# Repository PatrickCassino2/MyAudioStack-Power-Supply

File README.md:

# MyAudioStack-Power-Supply
A +/- 17V Offline Power Supply Compatible with MyAudioStack

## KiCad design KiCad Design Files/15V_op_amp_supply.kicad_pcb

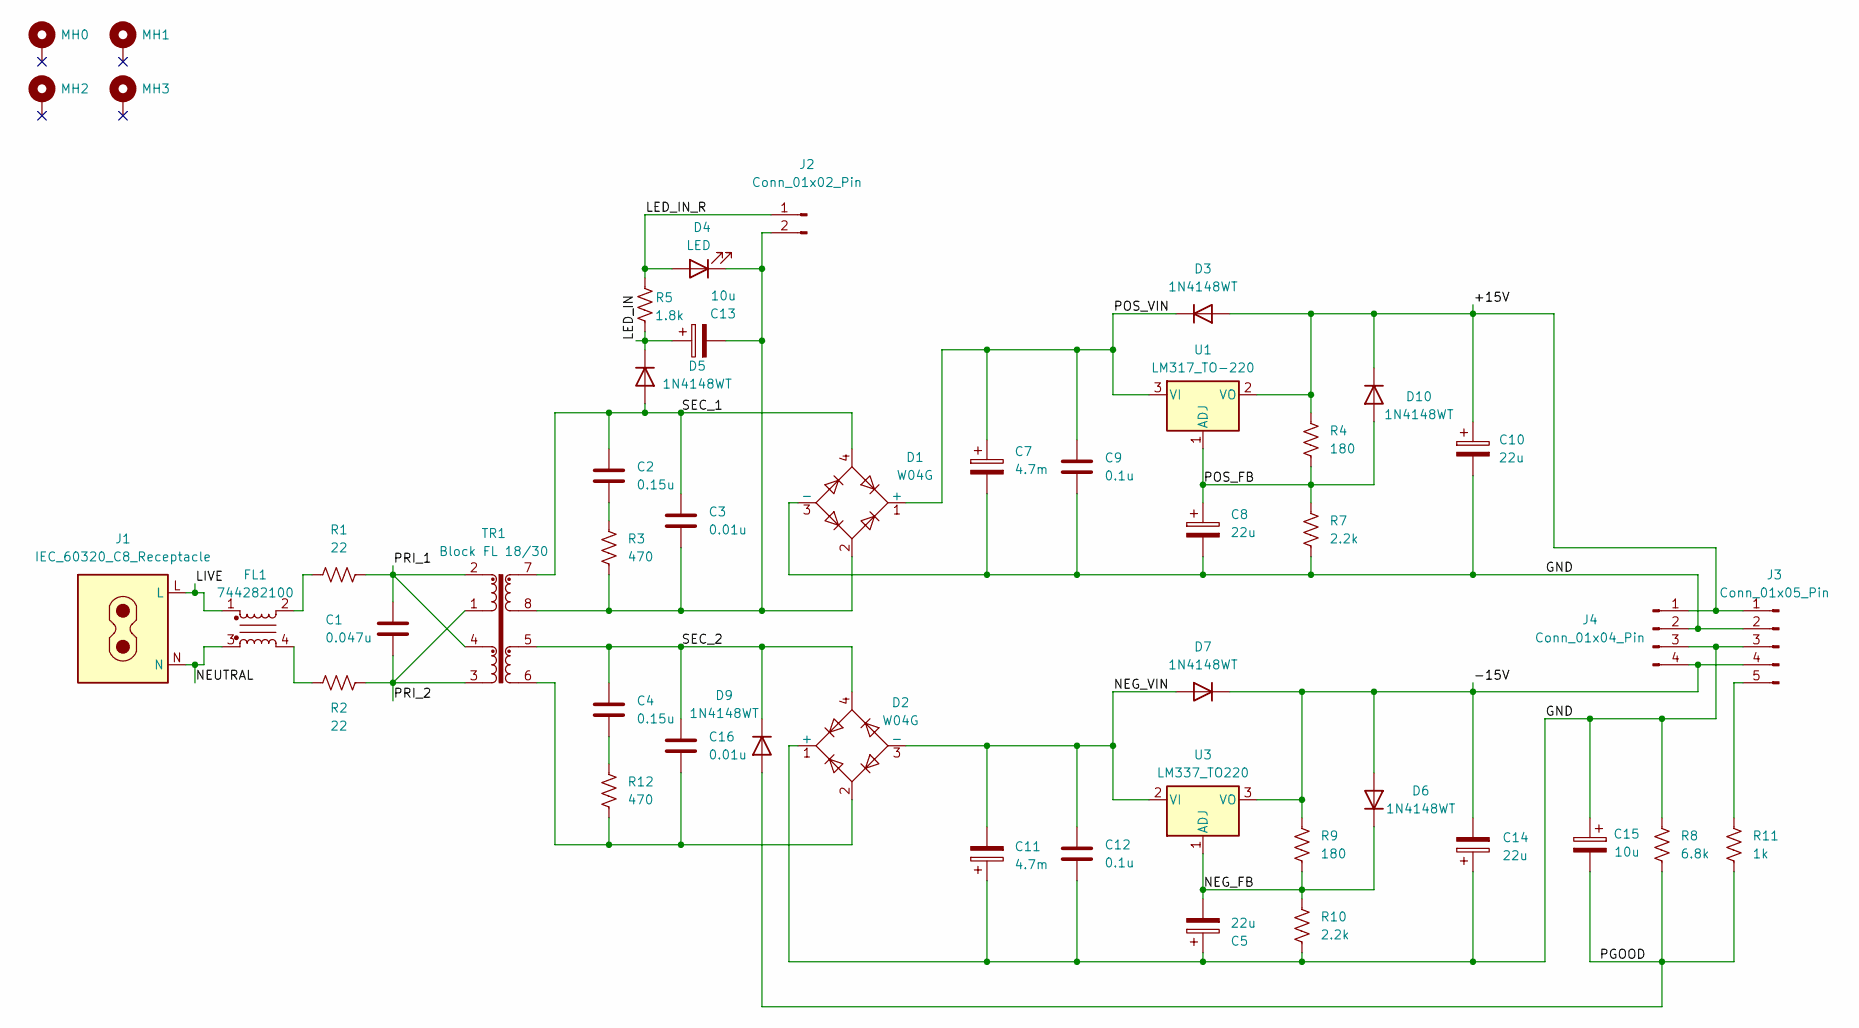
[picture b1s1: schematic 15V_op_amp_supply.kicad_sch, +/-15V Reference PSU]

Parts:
C1: 0.047u; C_Rect_L18.0mm_W5.0mm_P15.00mm_FKS3_FKP3
C2, C4: 0.15u; C_Rect_L10.3mm_W5.0mm_P7.50mm_MKS4
C3, C16: 0.01u; C_Rect_L7.2mm_W2.5mm_P5.00mm_FKS2_FKP2_MKS2_MKP2
C5, C8, C10, C14: 22u; CP_Radial_D5.0mm_P2.00mm
C7, C11: 4.7m; CP_Radial_D25.0mm_P10.00mm_SnapIn
C9, C12: 0.1u; C_Rect_L7.2mm_W2.5mm_P5.00mm_FKS2_FKP2_MKS2_MKP2
C13, C15: 10u; CP_Radial_D5.0mm_P2.00mm
D1, D2: W04G; Diode_Bridge_Round_D9.8mm
D3, D5, D6, D7, D9, D10: 1N4148WT; D_SOD-123
D4: LED; LED_D3.0mm
FL1: 744282100; L_Bourns_SRF1260
J1: IEC_60320_C8_Receptacle; SWITCHCRAFT_RAPC322X
J2: Conn_01x02_Pin; PinHeader_1x02_P2.54mm_Vertical
J3: Conn_01x05_Pin; PinHeader_1x05_P2.54mm_Vertical
J4: Conn_01x04_Pin; PinHeader_1x04_P2.54mm_Vertical
MH0, MH1, MH2, MH3: MountingHole_Pad; MountingHole_3.2mm_M3_DIN965_Pad
R1, R2: 22; R_2512_6332Metric
R3, R12: 470; R_1206_3216Metric
R4, R9: 180; R_1206_3216Metric
R5: 1.8k; R_1206_3216Metric
R7, R10: 2.2k; R_1206_3216Metric
R8: 6.8k; R_1206_3216Metric
R11: 1k; R_1206_3216Metric
TR1: Block FL 18/30; FL18_30
U1: LM317_TO-220; TO-220-3_Vertical
U3: LM337_TO220; TO-220-3_Vertical

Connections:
/+15V: C10.1, D3.2 (A), D10.1 (K), J3.1, J4.1, R4.1, U1.2 (VO)
/-15V: C14.2, D6.2 (A), D7.1 (K), J3.4, J4.4, R9.1, U3.3 (VO)
/GND: C5.1, C7.2, C8.2, C9.2, C10.2, C11.1, C12.2, C14.1, C15.1, D1.3 (-), D2.1 (+), J3.2, J3.3, J4.2, J4.3, R7.2, R8.1, R10.2
/LED_IN: C13.1, D5.1 (K), R5.2
/LED_IN_R: D4.2 (A), J2.1, R5.1
/LIVE: FL1.1, J1.L
/NEG_FB: C5.2, D6.1 (K), R9.2, R10.1, U3.1 (ADJ)
/NEG_VIN: C11.2, C12.1, D2.3 (-), D7.2 (A), U3.2 (VI)
/NEUTRAL: FL1.3, J1.N
/PGOOD: C15.2, D9.2 (A), R8.2, R11.2
/POS_FB: C8.1, D10.2 (A), R4.2, R7.1, U1.1 (ADJ)
/POS_VIN: C7.1, C9.1, D1.1 (+), D3.1 (K), U1.3 (VI)
/PRI_1: C1.1, R1.2, TR1.2, TR1.4
/PRI_2: C1.2, R2.2, TR1.1, TR1.3
/SEC_1: C2.1, C3.1, D1.4, D5.2 (A), TR1.7
/SEC_2: C4.1, C16.1, D2.4, D9.1 (K), TR1.5
unnamed: C2.2, R3.2
unnamed: C4.2, R12.2
unnamed: C16.2, D2.2, R12.1, TR1.6
unnamed: C3.2, C13.2, D1.2, D4.1 (K), J2.2, R3.1, TR1.8
unnamed: FL1.2, R1.1
unnamed: FL1.4, R2.1
unnamed: J3.5, R11.1

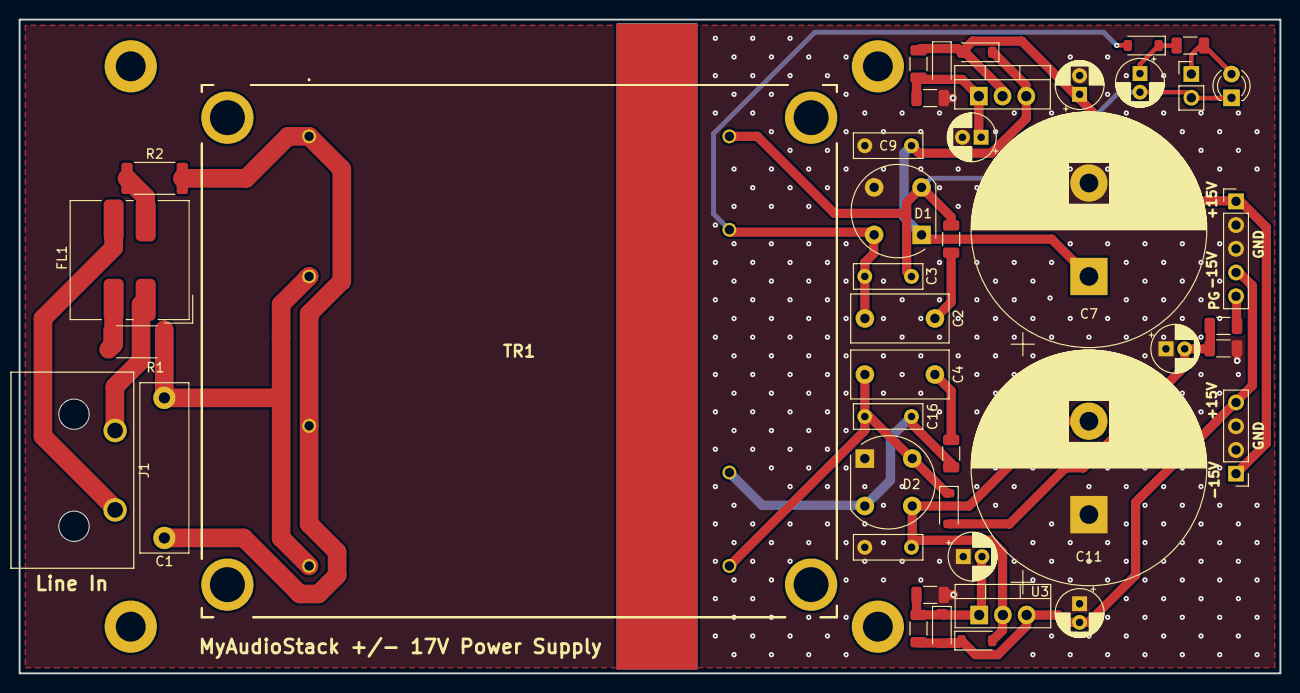
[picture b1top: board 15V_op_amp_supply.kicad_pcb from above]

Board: 2 copper layers, 135.0 x 70.0 mm, 47 parts (0 on the bottom side), 23 nets.

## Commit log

2025-01-27 Initial commit of design and mfg files
